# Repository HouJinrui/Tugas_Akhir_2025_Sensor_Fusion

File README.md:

# Tugas_Akhir_2025_Sensor_Fusion

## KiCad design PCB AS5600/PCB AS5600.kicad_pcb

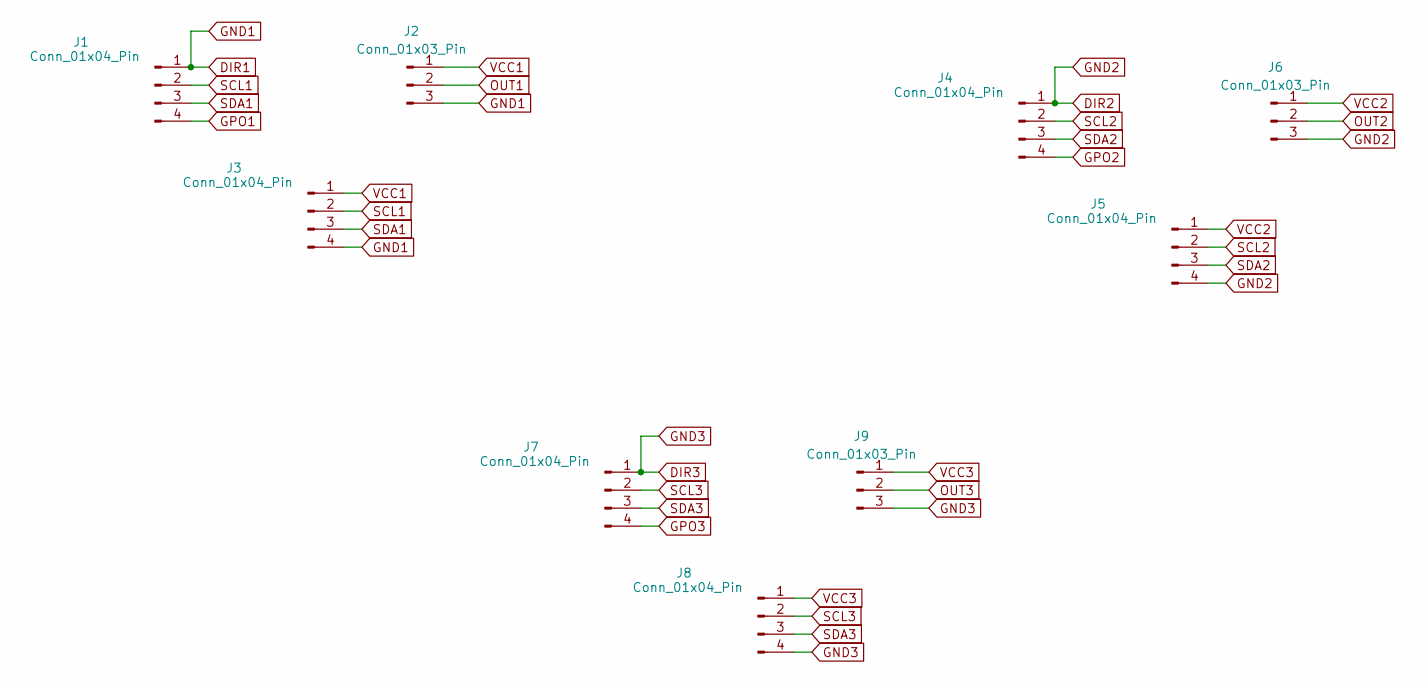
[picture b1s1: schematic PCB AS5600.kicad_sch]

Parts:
J1, J3, J4, J5, J7, J8: Conn_01x04_Pin; PinHeader_1x04_P2.54mm_Vertical
J2, J6, J9: Conn_01x03_Pin; PinHeader_1x03_P2.54mm_Vertical

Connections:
DIR1: J1.1, J2.3, J3.4
DIR2: J4.1, J5.4, J6.3
DIR3: J7.1, J8.4, J9.3
GPO1: J1.4
GPO2: J4.4
GPO3: J7.4
OUT1: J2.2
OUT2: J6.2
OUT3: J9.2
SCL1: J1.2, J3.2
SCL2: J4.2, J5.2
SCL3: J7.2, J8.2
SDA1: J1.3, J3.3
SDA2: J4.3, J5.3
SDA3: J7.3, J8.3
VCC1: J2.1, J3.1
VCC2: J5.1, J6.1
VCC3: J8.1, J9.1

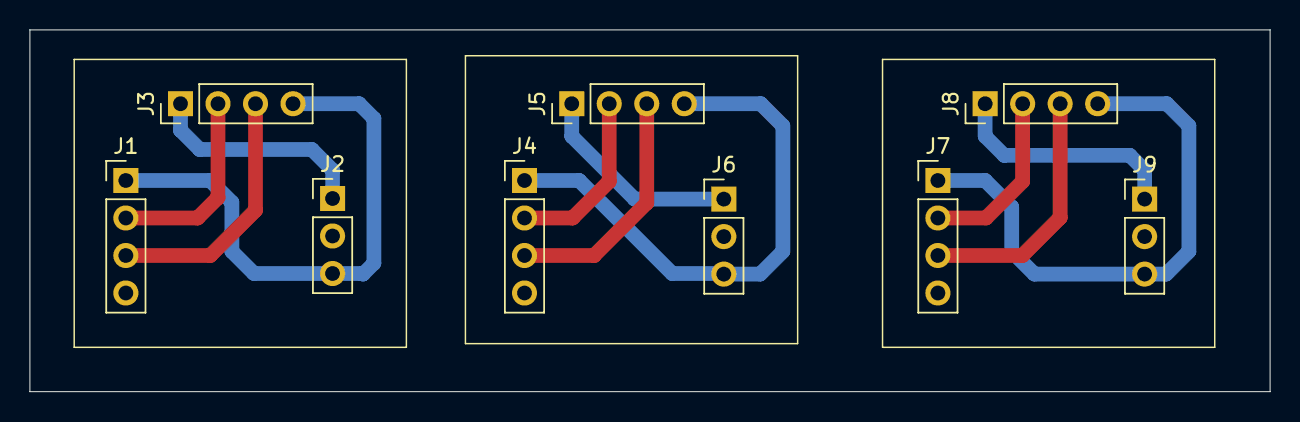
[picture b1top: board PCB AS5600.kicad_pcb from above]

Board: 2 copper layers, 84.0 x 24.5 mm, 9 parts (0 on the bottom side), 12 nets.
